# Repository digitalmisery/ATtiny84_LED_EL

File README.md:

ATtiny84 LED + EL
=======================
This board was designed as a small and simple
way to sequence LEDs and electroluminescent (EL)
wire using PWM. The ATtiny84 was chosen not only
because of its small size but also so I could
test out the [ATTinyCore](http://github.com/TCWORLD/ATTinyCore) bootloader.

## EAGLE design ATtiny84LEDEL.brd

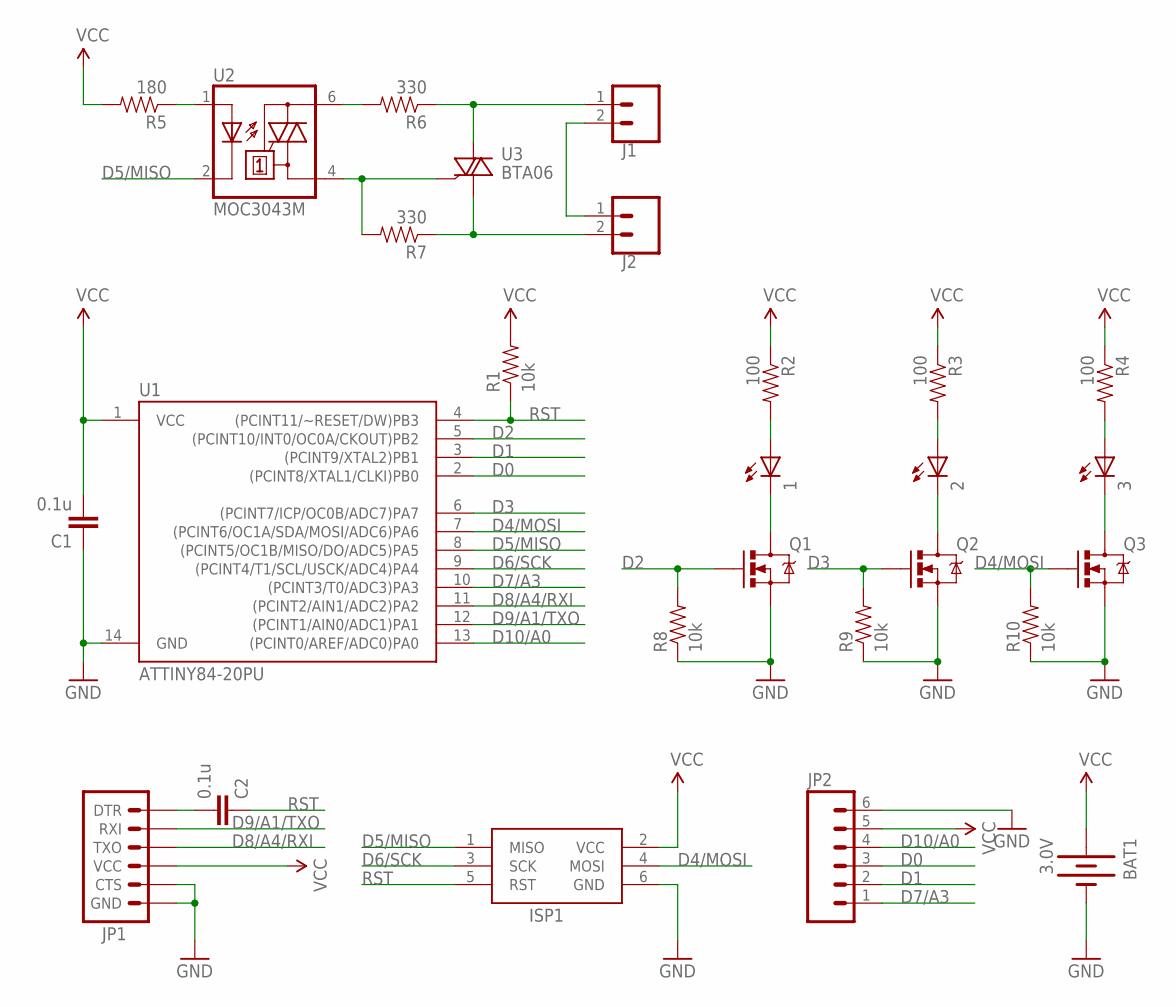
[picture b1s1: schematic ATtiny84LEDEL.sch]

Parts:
1, 2, 3: LED5MM
BAT1: 3.0V; JEELABS_BATTCOM_20MM_PTH
C1, C2: 0.1u; CAP-PTH-SMALL
ISP1: AVRISP-6; AVRISP
J1, J2: M025MM; SCREWTERMINAL-5MM-2
JP1: ARDUINO_SERIAL_PROGRAMLONGPADS; 1X06_LONGPADS
JP2: M06LONGPADS; 1X06_LONGPADS
Q1, Q2, Q3: MOSFET-NCHANNELPTH; TO-92
R1, R8, R9, R10: 10k; AXIAL-0.4
R2, R3, R4: 100; AXIAL-0.4
R5: 180; AXIAL-0.4
R6, R7: 330; AXIAL-0.4
U1: ATTINY84-20PU; DIL14
U2: MOC3043M; DIL06
U3: BTA06; TO220AB

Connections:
AC1: J1.1, R6.P$1 (1), U3.2 (A2)
AC2: J1.2, J2.1
AC3: J2.2, R7.P$1 (1), U3.1 (A1)
D0: JP2.3, U1.2 ((PCINT8/XTAL1/CLKI)PB0)
D1: JP2.2, U1.3 ((PCINT9/XTAL2)PB1)
D2: Q1.2 (G), R8.P$2 (2), U1.5 ((PCINT10/INT0/OC0A/CKOUT)PB2)
D3: Q2.2 (G), R9.P$2 (2), U1.6 ((PCINT7/ICP/OC0B/ADC7)PA7)
D4/MOSI: ISP1.4 (MOSI), Q3.2 (G), R10.P$2 (2), U1.7 ((PCINT6/OC1A/SDA/MOSI/ADC6)PA6)
D5/MISO: ISP1.1 (MISO), U1.8 ((PCINT5/OC1B/MISO/DO/ADC5)PA5), U2.2 (C)
D6/SCK: ISP1.3 (SCK), U1.9 ((PCINT4/T1/SCL/USCK/ADC4)PA4)
D7/A3: JP2.1, U1.10 ((PCINT3/T0/ADC3)PA3)
D8/A4/RXI: JP1.3 (TXO), U1.11 ((PCINT2/AIN1/ADC2)PA2)
D9/A1/TXO: JP1.2 (RXI), U1.12 ((PCINT1/AIN0/ADC1)PA1)
D10/A0: JP2.4, U1.13 ((PCINT0/AREF/ADC0)PA0)
GND: BAT1.2 (-), C1.1, ISP1.6 (GND), JP1.5 (CTS), JP1.6 (GND), JP2.6, Q1.3 (S), Q2.3 (S), Q3.3 (S), R8.P$1 (1), R9.P$1 (1), R10.P$1 (1), U1.14 (GND)
unnamed: C2.2, JP1.1 (DTR)
unnamed: R5.P$1 (1), U2.1 (A)
unnamed: 1.K (C), Q1.1 (D)
unnamed: 2.K (C), Q2.1 (D)
unnamed: R6.P$2 (2), U2.6 (A2)
unnamed: 3.K (C), Q3.1 (D)
unnamed: R7.P$2 (2), U2.4 (A1), U3.3 (G)
unnamed: 1.A, R2.P$2 (2)
unnamed: 2.A, R3.P$2 (2)
unnamed: 3.A, R4.P$2 (2)
RST: C2.1, ISP1.5 (RST), R1.P$1 (1), U1.4 ((PCINT11/~RESET/DW)PB3)
VCC: BAT1.1 (+), C1.2, ISP1.2 (VCC), JP1.4 (VCC), JP2.5, R1.P$2 (2), R2.P$1 (1), R3.P$1 (1), R4.P$1 (1), R5.P$2 (2), U1.1 (VCC)

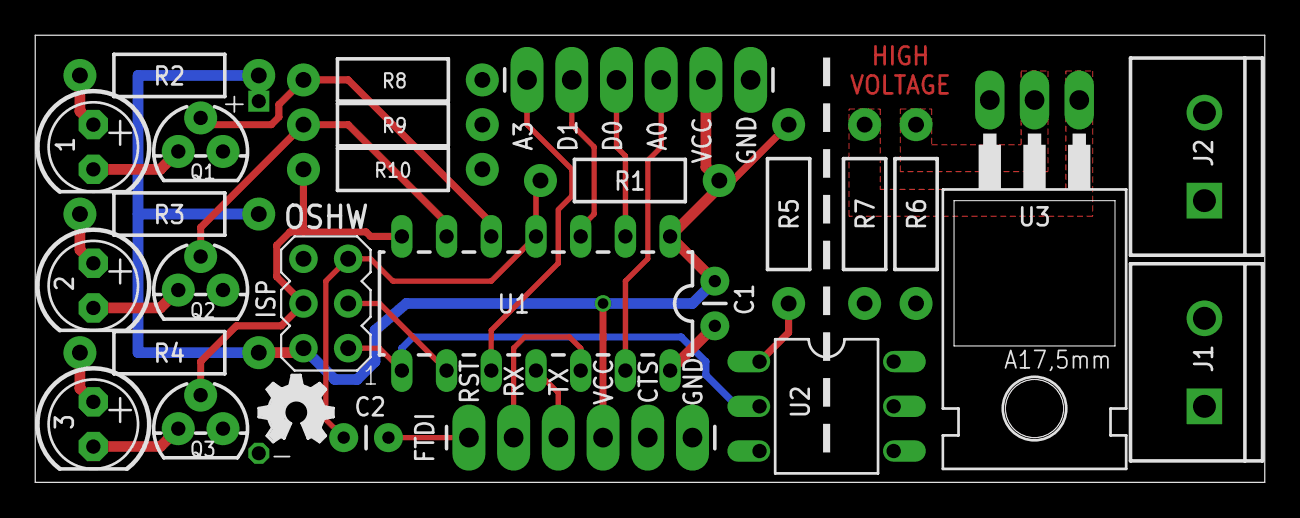
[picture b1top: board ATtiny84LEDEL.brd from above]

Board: 2 copper layers, 69.9 x 25.4 mm, 28 parts (1 on the bottom side), 27 nets.

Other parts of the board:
U$1: OSHW_FILLX150_NOTEXT

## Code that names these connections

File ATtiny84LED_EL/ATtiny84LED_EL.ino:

//*********************************************************************
//* ATtiny84 LED + EL 
//* by Paul Martis
//* http://www.digitalmisery.com
//* January 26, 2013
//*********************************************************************
//Hardware Definitions
// ATtiny84 (PDIP or SOIC - 14)
// Using ATTinyCore from https://github.com/TCWORLD/ATTinyCore
// [TYPE] FUNCTION (Arduino) Pin
//
//                             +-\/-+
//                       VCC  1|    |14  GND
//  [GPIO] D0    (D  0)  PB0  2|    |13  PA0  (D10,A0) D10/A0  [ADC/IO]
//  [GPIO] D1    (D  1)  PB1  3|    |12  PA1  (D9,A1)  TXO     [ADC/IO]
//         RESET (D 11)  PB3  4|    |11  PA2  (D8,A2)  RXI     [ADC/IO]
//  [PWM]  LED1  (D  2)  PB2  5|    |10  PA3  (D7,A3)  D7/A3   [ADC/IO]  
//  [PWM]  LED2  (D  3)  PA7  6|    |9   PA4  (D  6)   SPI_SCK
//  [PWM]  LED3  (D  4)  PA6  7|    |8   PA5  (D  5)   EL_OPTO [PWM]
//                             +----+
#define DIO_0 0
#define DIO_1 1
#define LED1 2
#define LED2 3
#define LED3 4
#define EL_OPTO 5
#define DIO_7 7
#define AI_3 3
#define DIO_8 8
#define RXI 8
#define AI_2 2
#define DIO_9 9
#define TXO 9
#define AI_1 1
#define DIO_10 10
#define AI_0 0

long current_time = 0;
//*********************************************************************
//Delay macros
#define LED_FADE_DURATION 1000
#define LED_DELAY ceil(LED_FADE_DURATION / 255)
#define EL_BPM 70
#define EL_DELAY ceil(60000 / EL_BPM / 2 / 255)
#define TIME_DELAY 120000
//*********************************************************************
//Setup function
void setup()
{
  pinMode(EL_OPTO, OUTPUT);
  pinMode(LED1, OUTPUT);
  pinMode(LED2, OUTPUT);
  pinMode(LED3, OUTPUT);
  digitalWrite(LED1, LOW);
  digitalWrite(LED2, LOW);
  digitalWrite(LED3, LOW);
  digitalWrite(EL_OPTO, HIGH);
  delay(3000);
  //Serial.begin(9600);
  for (int i = 0; i <=255; i++)
  {
    analogWrite(LED1, i);
    delay(LED_DELAY);
  }
  delay(500);
  for (int i = 0; i <=255; i++)
  {
    analogWrite(LED2, i);
    delay(LED_DELAY);
  }
  delay(500);
  for (int i = 0; i <=255; i++)
  {
    analogWrite(LED3, i);
    delay(LED_DELAY);
  }
  delay(500);
}
//*********************************************************************
//Main loop
void loop()
{
  if (millis() - current_time > TIME_DELAY)
  {
    current_time = millis();
    digitalWrite(LED1, LOW);
    digitalWrite(LED2, LOW);
    digitalWrite(LED3, LOW);
    digitalWrite(EL_OPTO, HIGH);
    delay(3000);
    for (int i = 0; i <=255; i++)
    {
      analogWrite(LED1, i);
      delay(LED_DELAY);
    }
    delay(500);
    for (int i = 0; i <=255; i++)
    {
      analogWrite(LED2, i);
      delay(LED_DELAY);
    }
    delay(500);
    for (int i = 0; i <=255; i++)
    {
      analogWrite(LED3, i);
      delay(LED_DELAY);
    }
    delay(500);
  }
  for (int i = 255; i >= 0; i--)
  {
    analogWrite(EL_OPTO, i);
    delay(EL_DELAY);
  }
  delay(EL_DELAY);
  for (int i = 0; i <=255; i++)
  {
    analogWrite(EL_OPTO, i);
    delay(EL_DELAY);
  }
//  digitalWrite(EL_OPTO, LOW);
//  Serial.println("Low");
//  delay(1000);
//  digitalWrite(EL_OPTO, HIGH);
//  Serial.println("High");
  delay(250);
}
//*********************************************************************

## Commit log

2013-08-01 Added Eagle PCB files and Arduino sketch.
2013-08-01 Updated Eagle PCB files.
2013-08-01 Added frame to schematic.

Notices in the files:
parts and their libraries:
SparkFun-DigitalIC: Licensing: CC v3.0 Share-Alike You are welcome to use this library for commercial purposes.
